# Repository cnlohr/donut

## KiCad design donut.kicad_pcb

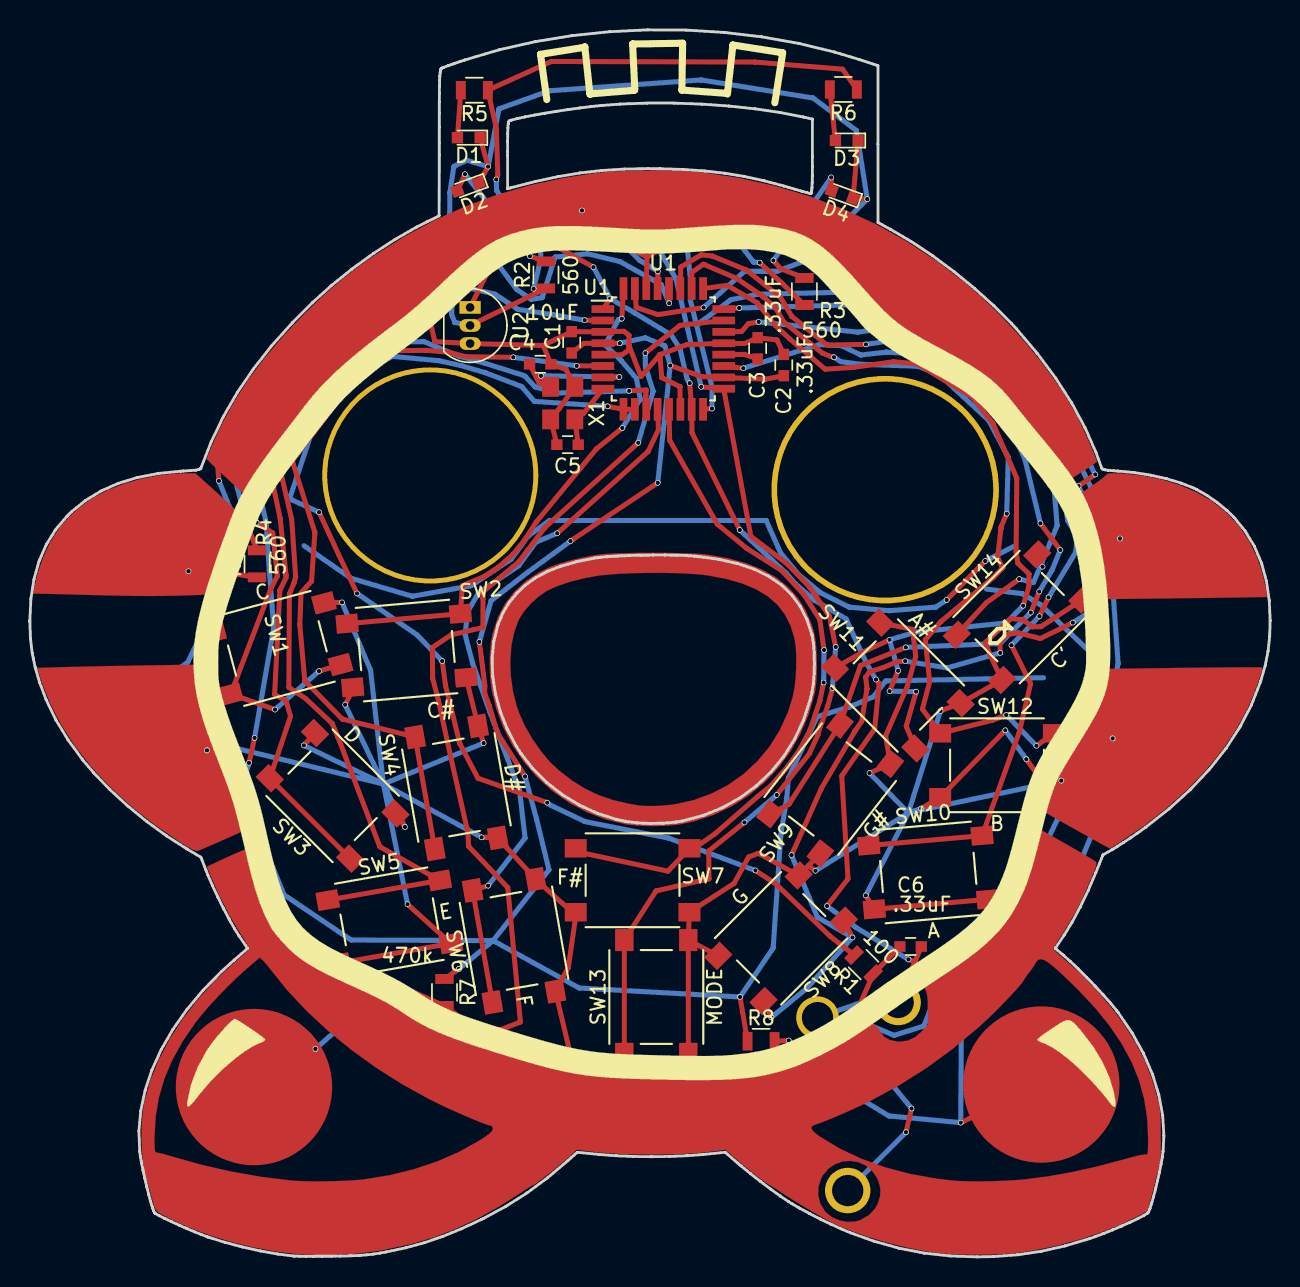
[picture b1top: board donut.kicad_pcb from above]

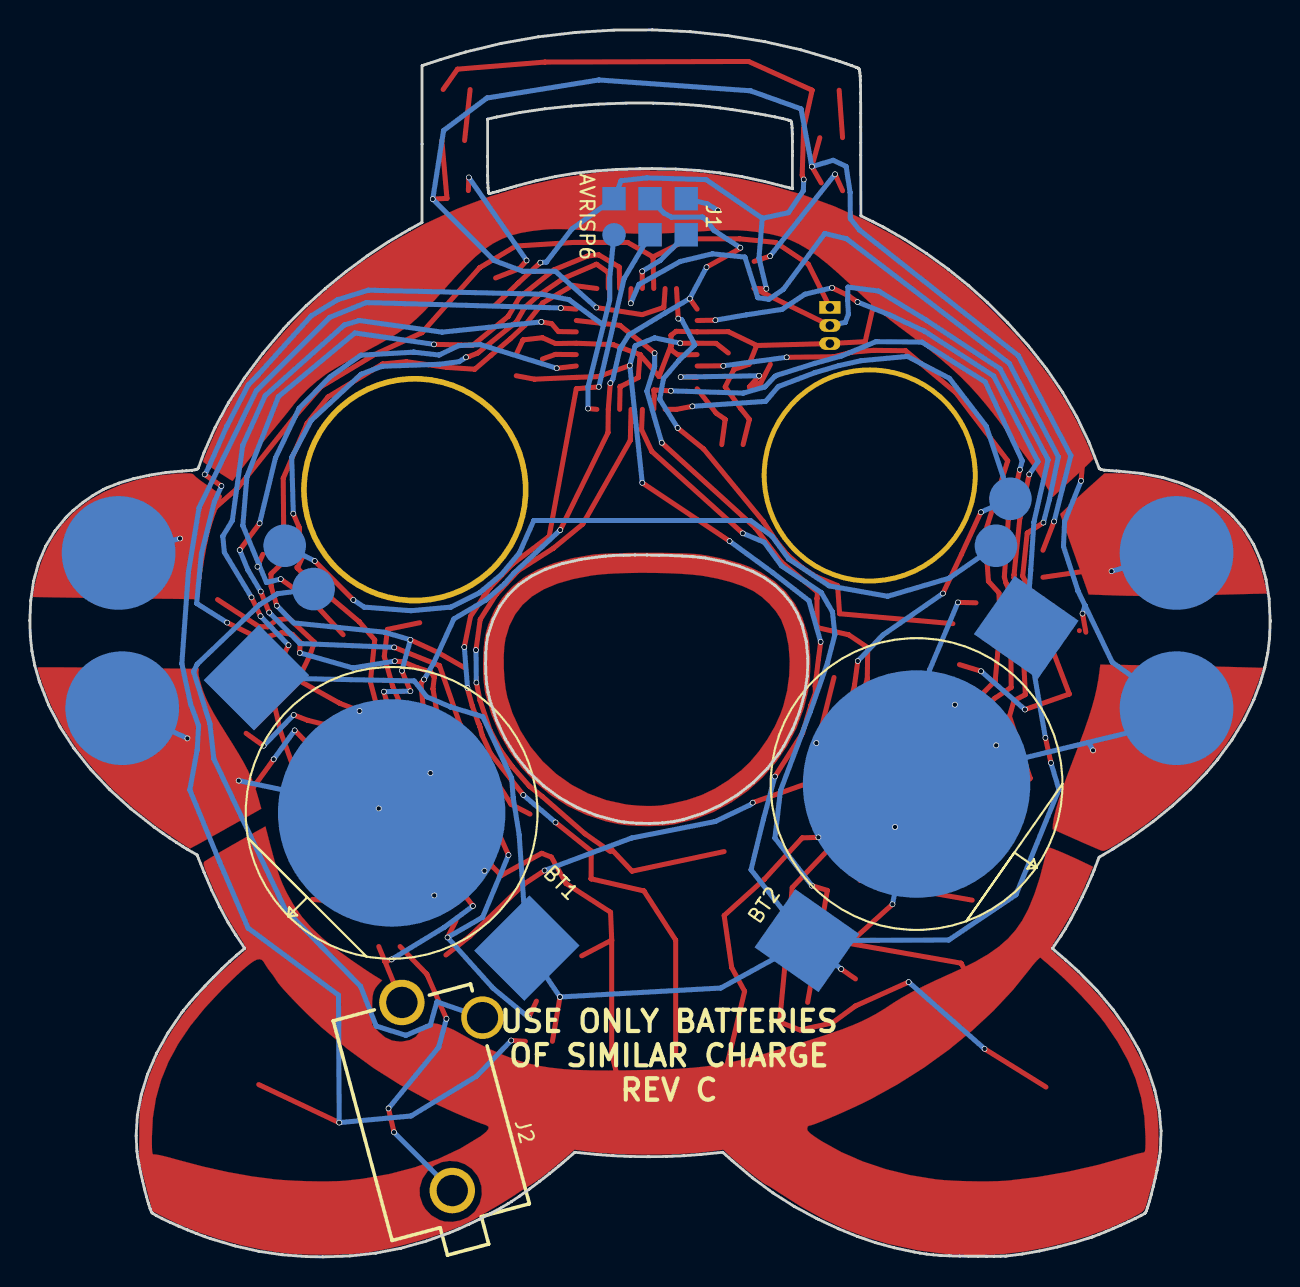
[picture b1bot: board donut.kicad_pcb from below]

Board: 2 copper layers, 87.3 x 86.3 mm, 54 parts (12 on the bottom side), 34 nets.

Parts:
BT1, BT2: Battery_Cell; S8211-45R
C1: 10uF; C_0603
C2, C3, C6: .33uF; C_0603
C4, C5: 10pF; C_0603
D1, D3: NP; LED_0603
D2, D4: RED; LED_0603
G0: PAD1; kingdonut2
J1: AVRISP6; RIBBON6SMT_POGO
J2: Jack; 3.5mm_barrel_jack_MJ-3536N
P1, P4, P8: PAD1; SMTPIN
P2, P3, P5, P6, P7, P9, P10, P11, P12, P13, P14: PAD2; SMTPIN
R1: 100; R_0805
R2, R3, R4: 560; R_0805
R5, R6: NP; R_0805
R7, R8: 470k; R_0805
SW1: C; TACTILE10Small
SW2: C#; TACTILE10Small
SW3: D; TACTILE10Small
SW4: D#; TACTILE10Small
SW5: E; TACTILE10Small
SW6: F; TACTILE10Small
SW7: F#; TACTILE10Small
SW8: G; TACTILE10Small
SW9: G#; TACTILE10Small
SW10: A; TACTILE10Small
SW11: A#; TACTILE10Small
SW12: B; TACTILE10Small
SW13: MODE; TACTILE10Small
SW14: C'; TACTILE10Small
U1: ATMEGA48PA-MU; TQFP-32_7x7mm_Pitch0.8mm
U2: TSDP343xx; TO-92_Inline_Narrow_Oval
X1: 12MHz; XTAL4P

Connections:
AUD: P12.1, R1.2, U1.9, U1.10
AUD-: C6.2, J1.4, J2.2, U1.1, U1.15
AUD-SM: J2.3, P14.1
GND: BT1.2, BT2.2, C1.2, C2.2, C3.2, C4.2, C5.2, J1.6, P3.1, P6.1, P9.1, P10.1, SW1.2, SW1.4, SW2.2, SW2.4, SW3.2, SW3.4, SW4.2, SW4.4, SW5.2, SW5.4, SW6.2, SW6.4, SW7.2, SW7.4, SW8.2, SW8.4, SW9.2, SW9.4, SW10.2, SW10.4, SW11.2, SW11.4, SW12.2, SW12.4, SW13.2, SW13.4, SW14.2, SW14.4, U1.3, U1.5, U1.14, U1.21, U2.3, X1.3, X1.4
MISO: J1.1, SW8.1, SW8.3, U1.16
unnamed: C3.1, U1.20
unnamed: C4.1, U1.7, X1.1
unnamed: C5.1, U1.8, X1.2
unnamed: C6.1, J2.1, R1.1
unnamed: D1.2, R5.2
unnamed: D2.2, R2.2
unnamed: D3.2, R6.2
unnamed: D4.2, R3.2
unnamed: P5.1, P7.1, R4.1
unnamed: P11.1, P13.1
RST: J1.5, U1.29
RX: P4.1, P8.1, U1.30, U2.1
SCK: J1.3, SW13.1, SW13.3, U1.17
TOUCH1: P2.1, R7.2, U1.23
TOUCH2: P1.1, R8.2, U1.24
TSW0: SW1.1, SW1.3, U1.28
TSW1: SW2.1, SW2.3, U1.32
TSW2: SW3.1, SW3.3, U1.2
TSW3: SW4.1, SW4.3, U1.6
TSW4: SW5.1, SW5.3, U1.11
TSW5: SW6.1, SW6.3, U1.12
TSW6: SW7.1, SW7.3, U1.13
TSW8: SW9.1, SW9.3, U1.19
TSW9: SW10.1, SW10.3, U1.22
TSW10: SW11.1, SW11.3, U1.25
TSW11: SW12.1, SW12.3, U1.26
TSW12: SW14.1, SW14.3, U1.27
TX: D1.1, D2.1, D3.1, D4.1, R4.2, U1.31
VCC: BT1.1, BT2.1, C1.1, C2.1, J1.2, R2.1, R3.1, R5.1, R6.1, R7.1, R8.1, U1.4, U1.18, U2.2

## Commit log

2017-09-06 Add artwork test
2017-09-06 Add original png
2017-10-12 update design
2017-10-30 Update schematic.
2017-10-31 Update donut
2017-11-06 add a tiny donut.
2017-11-06 Updated artwork
2017-11-18 update test firmware
2017-11-19 Update plots
2017-11-19 Udpate schematci
2017-12-13 Update utils.
2017-12-13 OK we're cookin with gas
2017-12-17 Huge change to the fundamental way the sound works, much higher quality.
2017-12-17 Update full thing with new audio format support
2017-12-18 Update with noise and volume!
2018-01-21 Add mode button
2018-01-21 Added more modes
2018-01-21 Added MAG
2018-01-21 Add drums
2018-01-21 fix break
2018-01-21 Merged
2018-01-21 Added raws
2018-01-21 Added Nick mode
2018-01-21 Add programmable drum kits
2018-01-21 Fixed fest
2018-01-21 Added roar
2018-01-21 reverse mode 6
2018-01-21 Added watchdog and eeprom resume
2018-01-21 Fixed max mode number
2018-01-21 Update drum kits
2018-01-21 Make synth slightly louder
2018-01-21 Fix Makefile for "burnall"
2018-01-21 Ready to burn?
2018-01-21 Everything but sleepQ
2018-01-21 Shippit
2018-01-21 Maybe fix lfsr?
2018-02-03 Fixed fuses
